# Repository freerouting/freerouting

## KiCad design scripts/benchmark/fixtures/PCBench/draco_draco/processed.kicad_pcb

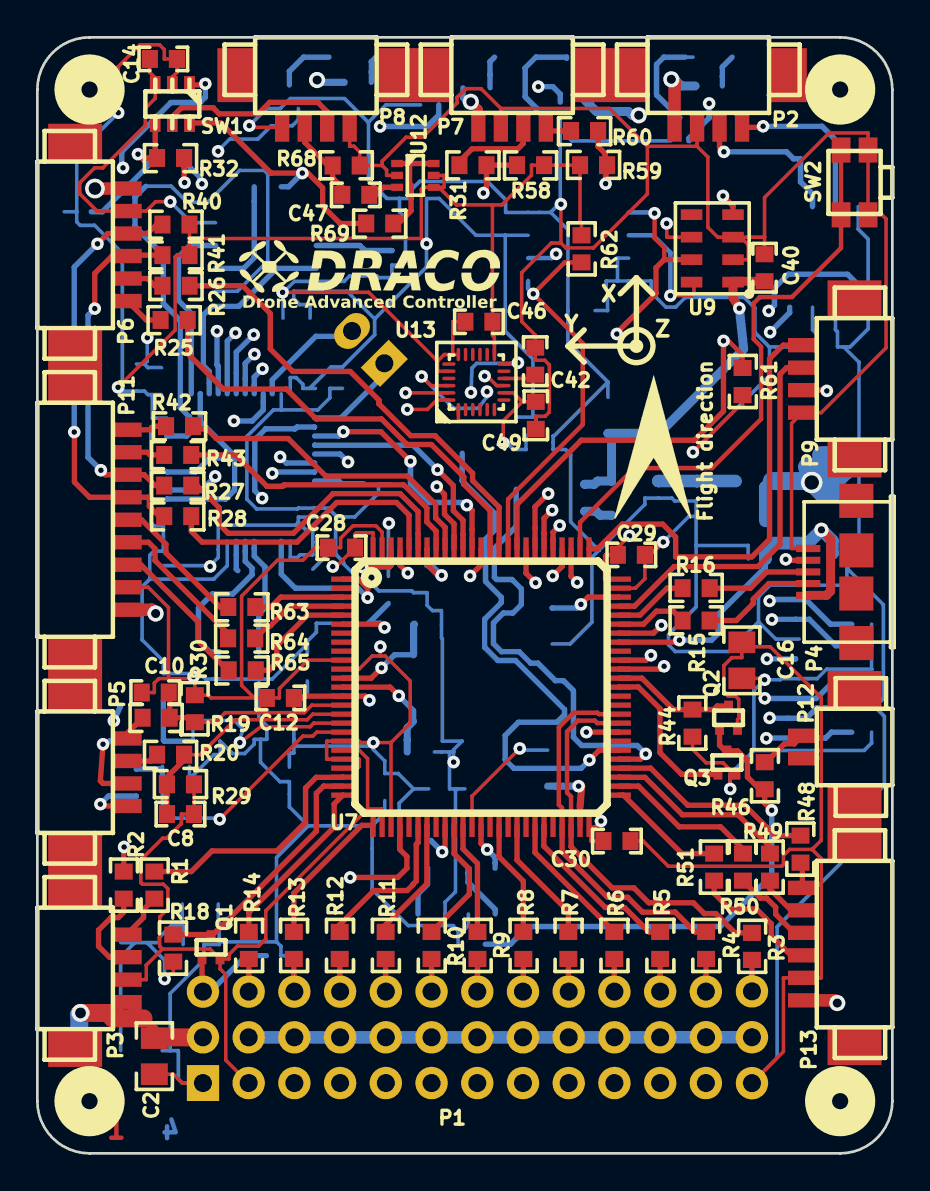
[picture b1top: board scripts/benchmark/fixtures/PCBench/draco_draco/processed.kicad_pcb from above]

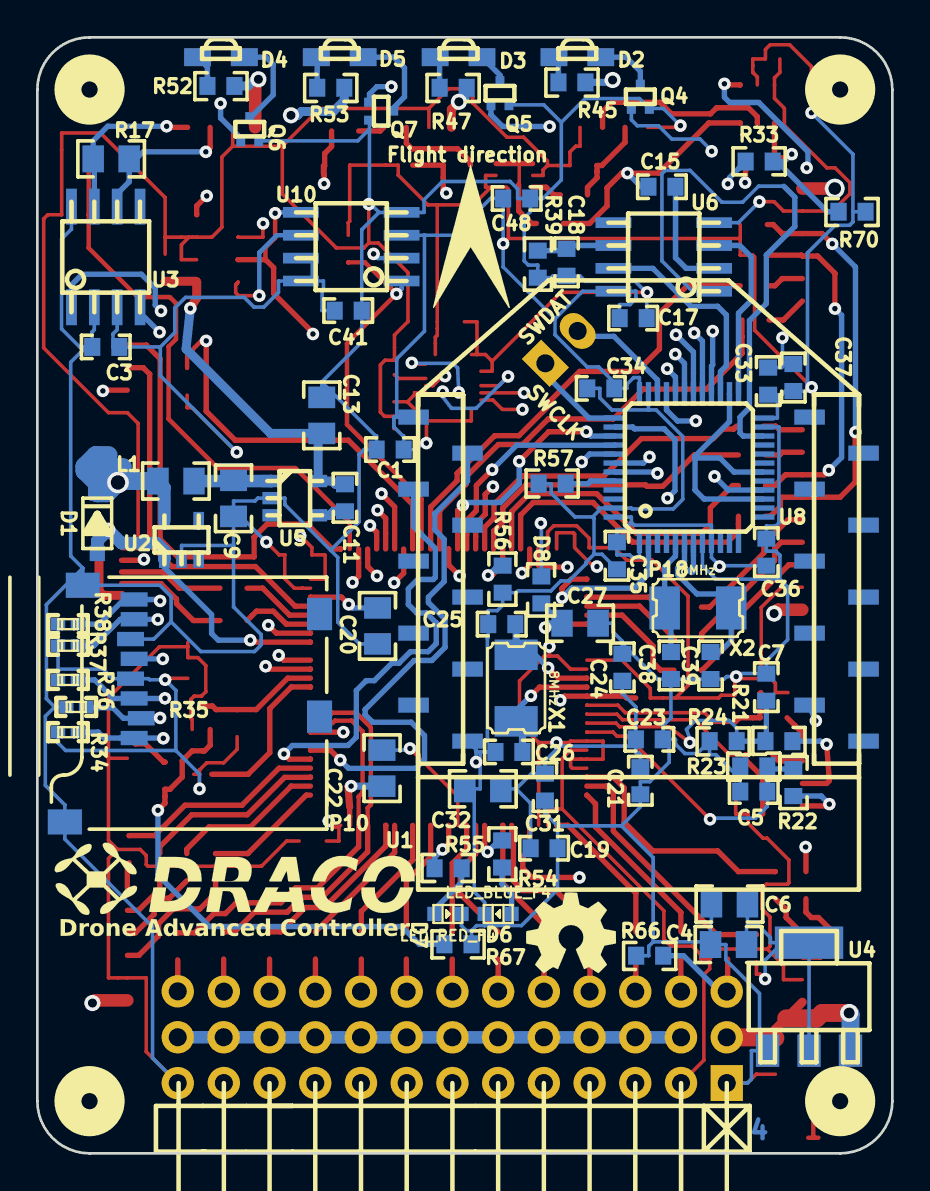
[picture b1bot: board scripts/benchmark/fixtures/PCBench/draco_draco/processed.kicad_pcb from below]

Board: 4 copper layers, 47.5 x 62.0 mm, 172 parts (83 on the bottom side), 154 nets.

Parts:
C1, C3, C5, C7, C8, C10, C12, C14, C15, C17, C19, C21, C23, C24, C28, C29, C30, C33, C34, C35, C36, C40, C41, C42, C46, C47, C48: 100nF; c_0603
C2, C4, C32: 4.7uF; c_0805
C6, C13, C27: 10uF; c_0805
C9: 1uF; c_0805
C11, C49: 10nF; c_0603
C16: 22uF; c_0805
C18: 56nF; c_0603
C20, C22: 2.2uF; c_0805
C25, C26, C38, C39: 18pF; c_0603
C31: 1uF; c_0603
C37: 4.7uF; c_0603
D1: PMEG6010CEH; sod123
D2: LED_RED; led_2.1x0.6
D3: LED_ORANGE; led_2.1x0.6
D4: LED_BLUE; led_2.1x0.6
D5: LED_GREEN; led_2.1x0.6
D6: LED_BLUE_F4; Led_0603
D7: LED_RED_F4; Led_0603
D8: CD0603-S01575; r_0603
G1, G3: DUMMY; ARROW
G2, G4: DUMMY; LOGOGO
G5: DUMMY; Logo_silk_OSHW_6x6mm
L1: 10uH; r_0805
P1: CONN_13X3; pin_strip_13x3-90
P2, P3, P5, P7, P8, P9: CONN_4; picoblade_4-90
P4: MICROUSB; conn_usb_B_micro_smd-FCI
P6, P13: CONN_6; picoblade_6-90
P10: MICROSD; MICRO-SD-SOCKET-PP
P11: CONN_9; picoblade_9-90
P12: CONN_2; picoblade_2-90
P14: CONN_2; pin_strip_2
P18: CONN_1; testpoint_pad
P19, P20, P21, P22: CONN_1; 1pin
Q1, Q2: NTA4153NT1G; sc75
Q3: NTA4151PT1G; sc75
Q4, Q5, Q6, Q7: PDTC114EE; sc75
R1, R2, R3, R4, R5, R6, R7, R8, R9, R10, R11, R12, R13, R14, R25, R26, R33, R42, R43, R46, R48, R49, R50, R51, R63, R64, R65: 470R; r_0603
R15, R16: 22R; r_0603
R17: 120R; r_0805
R18, R44, R58, R59: 4k7; r_0603
R19, R20, R21, R24, R29, R30, R56, R57, R61, R62, R66, R67: 39k; r_0603
R22: 82k; r_0603
R23: 12k; r_0603
R27, R28, R31, R32, R53, R60, R70: 220R; r_0603
R34, R36, R37, R38: 39k; r_0402
R35: 1M; r_0402
R39: 681k; r_0603
R40, R41: 4.7k; r_0603
R45, R47, R55: 330R; r_0603
R52: 180R; r_0603
R54: 100R; r_0603
R68, R69: 75R; r_0603
SW1: STG719; sot23-6
SW2: EVQP7A01K; EVQP7J01K
U1: XBEE; xbee-smt
U2: LTC4411; sot23-5
U3: SN65HVD233; so-8
U4: ADP3338AKCZ-3.3; stabil_sot223_1
U5: LT1761-3.3; tsot-5
U6: EL1883; so-8
U7: STM32F427VIT6; TQFP-100
U8: STM32F303CC; lqfp48
U9: MS5611
U10: FLASH-SPI-SO8; so-8
U12: MAX4090; sc70-6_2
U13: MPU-9250; dandys_qfn24-3x3
X1, X2: 8MHz; crystal_smd_5x3.2mm

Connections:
+3.3V: C1.2, C3.1, C4.1, C6.1, C14.2, C16.1, C17.2, C19.1, C21.1, C23.1, C24.1, C28.1, C29.1, C30.1, C31.1, C32.1, C33.2, C34.2, C35.2, C36.2, C37.2, C41.1, C46.1, C48.1, C49.1, D8.1, P10.4, Q3.2, R18.2, R34.2, R36.2, R37.2, R38.2, R40.2, R41.2, R44.2, R58.2, R59.2, R61.1, R62.2, R70.2, SW1.2, U1.1, U3.3, U4.OUT, U6.8, U7.11, U7.19, U7.21, U7.22, U7.28, U7.50, U7.75, U7.100, U8.1, U8.9, U8.24, U8.36, U8.48, U10.3, U10.7, U10.8, U12.4, U12.5, U13.1, U13.8, U13.13
+3.3VADC: C11.1, C13.1, C40.1, U5.5, U9.1
+5V: C2.1, D1.2, L1.1, P1.2, P1.5, P1.8, P1.11, P1.14, P1.17, P1.20, P1.23, P1.26, P1.29, P1.32, P1.35, P1.38, P2.4, P3.4, P6.1, P7.4, P11.9, P13.1, R45.2, R47.2, R52.2, R53.2, U2.5, U4.IN
AD0: C5.2, R22.2, R23.2, U7.18
AD1: C7.2, R21.2, R24.2, U7.17
AD2: C8.2, R20.2, R29.2, U7.16
AD3: C10.2, R19.2, R30.2, U7.15
CAN_RX: U3.4, U7.81
CAN_TX: U3.1, U7.82
EXTGPIO1: R65.2, U7.5
EXTGPIO2: R64.2, U7.4
EXTGPIO3: R63.2, U7.3
EXTI2C_SCL: R27.2, U7.95
EXTI2C_SDA: R28.2, U7.96
EXTSPI_CS: R51.1, U7.51
EXTSPI_MISO: R49.1, U7.53
EXTSPI_MOSI: R48.1, U7.54
EXTSPI_SCK: R50.1, U7.52
EXTUART1_RX: R43.2, U7.93
EXTUART1_TX: R42.2, U7.92
EXTUART2_RX: R31.2, R58.1, U8.43
EXTUART2_TX: R59.1, R60.2, U8.42
F3_CS: U7.98, U8.38
F3_INT: U7.1, U8.2
F4_NRST: C12.2, P9.2, U7.14
F4_SWCLK: P9.4, U7.76
F4_SWDIO: P9.3, U7.72
FLASH_CS: R62.1, U7.85, U10.1
GND: C1.1, C2.2, C3.2, C4.2, C5.1, C6.2, C7.1, C8.1, C9.2, C10.1, C12.1, C13.2, C14.1, C16.2, C17.1, C18.1, C19.2, C20.2, C21.2, C22.2, C23.2, C24.2, C25.2, C26.2, C27.2, C28.2, C29.2, C30.2, C31.2, C32.2, C33.1, C34.1, C35.1, C36.1, C37.1, C38.2, C39.2, C40.2, C41.2, C42.2, C46.2, C48.2, C49.2, D6.2, D7.2, P1.1, P1.4, P1.7, P1.10, P1.13, P1.16, P1.19, P1.22, P1.25, P1.28, P1.31, P1.34, P1.37, P2.3, P3.3, P4.5, P6.2, P7.3, P8.1, P8.4, P9.1, P10.6, P10.GND, P11.8, P12.1, P13.2, Q1.2, Q2.2, Q4.2, Q5.2, Q6.2, Q7.2, R23.1, R24.1, R29.1, R30.1, R35.1, R39.1, R56.2, R57.2, R66.1, R67.2, R68.1, SW1.3, SW2.1, U1.10, U2.2, U3.2, U3.8, U4.GND, U5.2, U6.4, U7.10, U7.20, U7.27, U7.37, U7.74, U7.99, U8.8, U8.23, U8.35, U8.47, U9.2, U9.3, U10.4, U12.2, U13.18, U13.20
GPS_RX: R25.2, U7.87
GPS_TX: R26.2, U7.86
LED_BLUE: Q6.1, U8.33
LED_GREEN: Q7.1, U8.32
LED_ORANGE: Q5.1, U8.31
LED_RED: Q4.1, U8.30
MPU_CS: U7.88, U13.22
MPU_INT: U7.97, U13.12
MS_CS: R61.2, U7.84, U9.4
unnamed: C20.1, U7.73
unnamed: C22.1, U7.49
unnamed: C27.1, D8.2, U7.6
unnamed: R57.1, U8.44
unnamed: P18.1, U8.7
unnamed: C38.1, U8.5, X2.2
unnamed: R55.2, U7.38
unnamed: SW2.2, U7.77
unnamed: R56.1, U7.94
unnamed: P14.2, U8.34
unnamed: D7.1, R55.1
unnamed: C42.1, U13.10
unnamed: R54.2, U7.34
unnamed: D6.1, R54.1
unnamed: P14.1, U8.37
unnamed: C39.1, U8.6, X2.1
unnamed: C25.1, U7.12, X1.2
unnamed: C26.1, U7.13, X1.1
unnamed: D3.2, Q5.3
unnamed: D2.2, Q4.3
unnamed: P11.6, R64.1
unnamed: D5.2, Q7.3
unnamed: D4.2, Q6.3
unnamed: P7.2, R31.1
unnamed: P7.1, R60.1
unnamed: C15.1, R69.1, SW1.6
unnamed: R69.2, U12.1, U12.6
unnamed: R32.1, R33.1, R70.1, SW1.4
unnamed: P8.2, SW1.5
unnamed: P1.3, Q1.1, R66.2
unnamed: C47.2, P8.3, R68.2
unnamed: C47.1, U12.3
unnamed: P5.1, R19.1
unnamed: P5.2, R20.1
unnamed: P11.7, R65.1
unnamed: P11.5, R63.1
unnamed: P11.2, R43.1
unnamed: P11.1, R42.1
unnamed: P5.4, R22.1
unnamed: P5.3, R21.1
unnamed: C11.2, U5.4
unnamed: P6.4, P11.3, R27.1, R41.1
unnamed: P6.3, P11.4, R28.1, R40.1
unnamed: P6.6, R25.1
unnamed: P6.5, R26.1
unnamed: C9.1, L1.2, U5.1
unnamed: P4.3, R16.1
unnamed: P4.2, R15.1
unnamed: P3.1, R1.1
unnamed: P3.2, R2.1
unnamed: P2.1, R17.2, U3.7
unnamed: P2.2, R17.1, U3.6
unnamed: P1.6, R14.1
unnamed: P13.3, R51.2
unnamed: C18.2, R39.2, U6.6
unnamed: C15.2, U6.2
unnamed: P1.15, R11.1
unnamed: P1.12, R12.1
unnamed: P1.9, R13.1
unnamed: P1.39, R3.1
unnamed: P1.36, R4.1
unnamed: P1.27, R7.1
unnamed: P1.33, R5.1
unnamed: P1.30, R6.1
unnamed: P1.24, R8.1
unnamed: P1.21, R9.1
unnamed: P1.18, R10.1
unnamed: P12.2, R46.2
unnamed: Q2.1, Q3.3, R46.1, R67.1
unnamed: D5.1, R53.1
unnamed: D4.1, R52.1
unnamed: D3.1, R47.1
unnamed: P13.6, R48.2
unnamed: P13.5, R49.2
unnamed: P13.4, R50.2
unnamed: D2.1, R45.1
OSD_CSYNC: U6.1, U8.22
OSD_HSYNC: U6.7, U8.27
OSD_MISO_MASK: SW1.1, U8.16
OSD_MOSI_VOUT: R32.2, U8.28
OSD_PIXEL_CLOCK: U8.15, U8.18, U8.26
OSD_SYNCOUT: R33.2, U8.29
OSD_VSYNC: U6.3, U8.25
PWM1: R14.2, U7.25
PWM2: R13.2, U7.26
PWM3: R12.2, U7.31
PWM4: R11.2, U7.32
PWM5: R10.2, U7.35
PWM6: R9.2, U7.36
PWM7: R8.2, U7.40
PWM8: R7.2, U7.42
PWM9: R6.2, U7.44
PWM10: R5.2, U7.45
PWM11: R4.2, U7.47, U7.60
PWM12: R3.2, U7.48, U7.59
SBUS: Q1.3, R18.1, U7.24
SDIO_CLK: P10.5, U7.80
SDIO_CMD: P10.3, R36.1, U7.83
SDIO_D0: P10.7, R37.1, U7.65
SDIO_D1: P10.8, R38.1, U7.66
SDIO_D2: P10.1, R34.1, U7.78
SDIO_D3: P10.2, R35.2, U7.79
SON_ECHO: R1.2, U7.23
SON_TRIG: R2.2, U7.29
SPI_MISO: U7.90, U8.40, U9.6, U10.2, U13.9
SPI_MOSI: U7.91, U8.41, U9.7, U10.5, U13.24
SPI_SCK: U7.89, U8.39, U9.8, U10.6, U13.23
SPORT_RX: Q2.3, R44.1, U7.64
SPORT_TX: Q3.1, U7.63
USBDM: R15.2, U7.70
USBDP: R16.2, U7.71
USBVB: D1.1, P4.1, U2.1, U7.68
USB_ID: P4.4, U7.69
XBEE_CTS: U1.12, U7.58
XBEE_RX: U1.2, U7.56
XBEE_TX: U1.3, U7.55

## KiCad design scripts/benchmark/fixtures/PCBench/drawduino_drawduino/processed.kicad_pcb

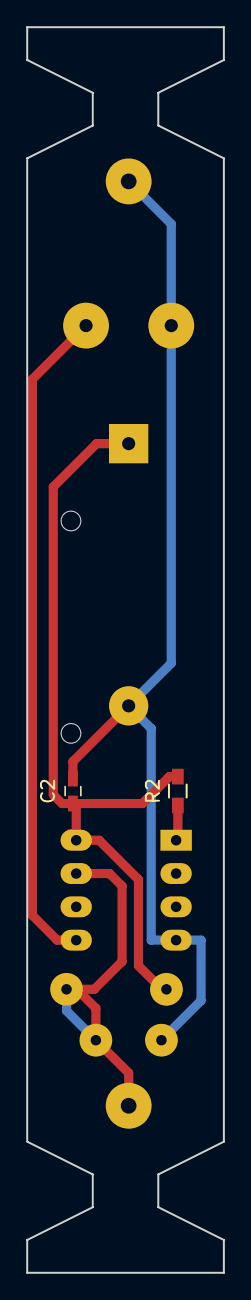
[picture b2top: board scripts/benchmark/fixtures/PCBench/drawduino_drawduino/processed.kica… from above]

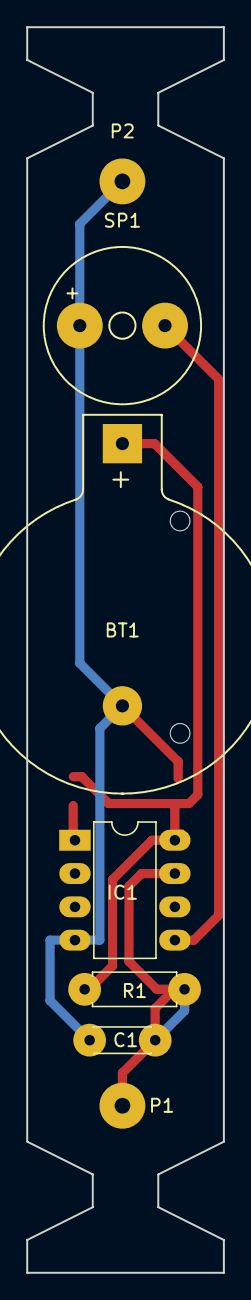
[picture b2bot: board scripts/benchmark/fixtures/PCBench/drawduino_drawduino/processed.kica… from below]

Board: 2 copper layers, 15.0 x 95.0 mm, 9 parts (7 on the bottom side), 5 nets.

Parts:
BT1: Battery; Keystone_103_1x20mm-CoinCell
C1: C; C_Disc_D4.3mm_W1.9mm_P5.00mm
C2: C; C_0603_HandSoldering
IC1: ATTINY85-P; DIP-8_W7.62mm_LongPads
P1, P2: CONN_01X01; SolderWirePad_single_1-2mmDrill
R1: R; R_Axial_DIN0207_L6.3mm_D2.5mm_P7.62mm_Horizontal
R2: R; R_0603_HandSoldering
SP1: SPEAKER; Buzzer_12x9.5RM7.6

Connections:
GND: BT1.2, C1.2, C2.2, IC1.4, P2.1, SP1.1
unnamed: C1.1, IC1.7, P1.1, R1.1
unnamed: IC1.1, R2.1
unnamed: IC1.5, SP1.2
VCC: BT1.1, C2.1, IC1.8, R1.2, R2.2

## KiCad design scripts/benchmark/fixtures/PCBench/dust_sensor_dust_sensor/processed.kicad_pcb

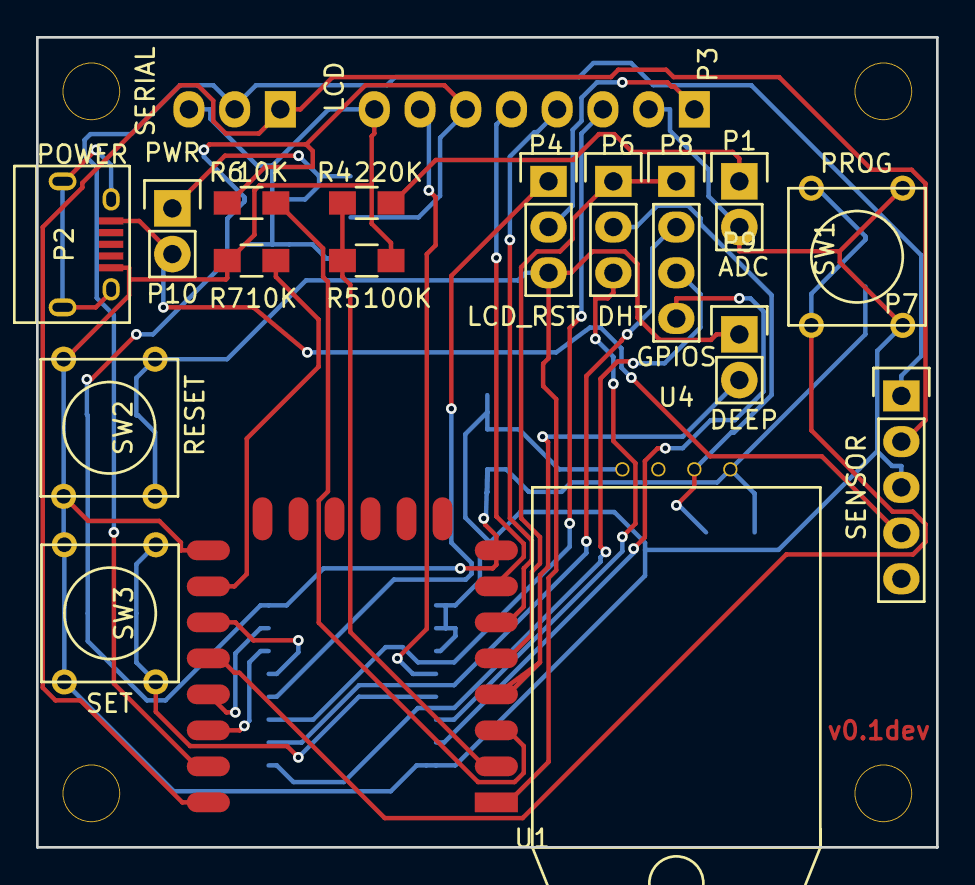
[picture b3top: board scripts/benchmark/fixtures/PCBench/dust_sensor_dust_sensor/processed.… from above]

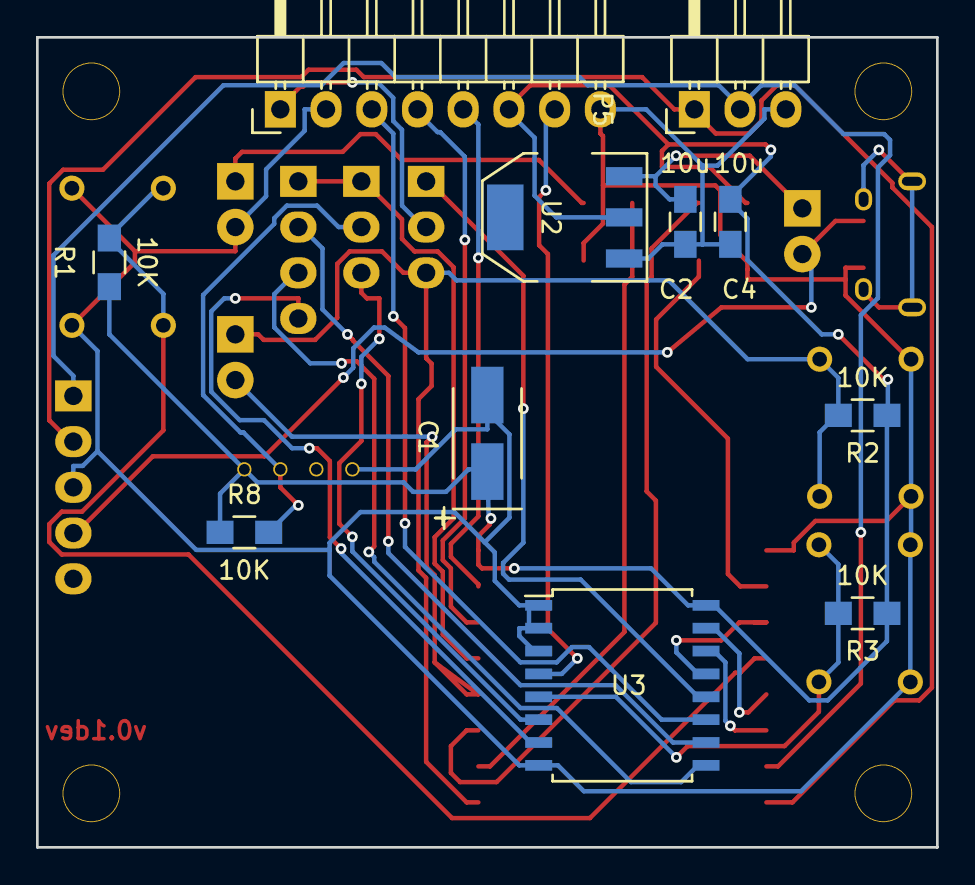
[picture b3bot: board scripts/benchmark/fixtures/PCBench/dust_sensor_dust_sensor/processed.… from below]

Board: 2 copper layers, 50.0 x 45.0 mm, 32 parts (11 on the bottom side), 29 nets.

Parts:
C1: 100u; TantalC_SizeB_EIA-3528_HandSoldering
C2, C4: 10u; C_0805_HandSoldering
Noname_1, Noname_2, Noname_3, Noname_4: hole_3mm
P1: ADC; Pin_Header_Straight_1x02
P2: POWER; USB_Micro-B
P3: LCD; Pin_Header_Angled_1x08
P4: LCD_RST; Pin_Header_Straight_1x03
P5: SERIAL; Pin_Header_Angled_1x03
P6: DHT; Pin_Header_Straight_1x03
P7: SENSOR; Pin_Header_Straight_1x05
P8: GPIOS; Pin_Header_Straight_1x04
P9: DEEP; Pin_Header_Straight_1x02
P10: PWR; Pin_Header_Straight_1x02
R1, R2, R3, R6, R7, R8: 10K; R_0805_HandSoldering
R4: 220K; R_0805_HandSoldering
R5: 100K; R_0805_HandSoldering
SW1: PROG; SW_PUSH_SMALL
SW2: RESET; SW_PUSH_SMALL
SW3: SET; SW_PUSH_SMALL
U1: ESP-12E
U2: AP1117; SOT-223
U3: PCF8574; SOIC-16_7.5x10.3mm_Pitch1.27mm
U4: DHT22; DHT22_nohole

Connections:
+3V3: C1.1, C4.1, P3.6, R1.1, R2.1, R3.1, R6.2, R8.1, U1.8, U2.2, U3.16, U4.1
+5V: P2.1, P7.4, P10.2
ADC: R4.2, R5.1, U1.2
DHT_EXT: P6.3, U3.6
DHT_GPIO: P6.1, P8.1, U1.5
GND: C1.2, C2.2, C4.2, P1.2, P2.5, P3.2, P3.8, P5.3, P7.3, R5.2, R7.2, SW1.2, SW2.2, SW3.2, U1.15, U2.1, U3.1, U3.2, U3.3, U3.8, U4.4
GPIO16: P9.2, U1.4
LIGHT: P3.7, U3.4
unnamed: C2.1, P10.1, U2.3
unnamed: P1.1, R4.1
unnamed: P3.1, P4.2
unnamed: P3.3, U3.11
unnamed: P3.4, U1.6
unnamed: P3.5, U1.7
unnamed: P4.1, U3.12
unnamed: P6.2, R8.2, U4.2
unnamed: R6.1, U1.3
unnamed: R7.1, U1.16
unnamed: U1.17, U3.13
unnamed: U1.19, U3.15
unnamed: U1.20, U3.14
P3: P8.4, U3.7
P4: P8.3, U3.9
P5: P8.2, U3.10
PROG: R1.2, SW1.1, U1.18
RESET: P4.3, P9.1, R2.2, SW2.1, U1.1
RX: P5.2, P7.1, U1.21
SET: R3.2, SW3.1, U3.5
TX: P5.1, P7.2, U1.22
